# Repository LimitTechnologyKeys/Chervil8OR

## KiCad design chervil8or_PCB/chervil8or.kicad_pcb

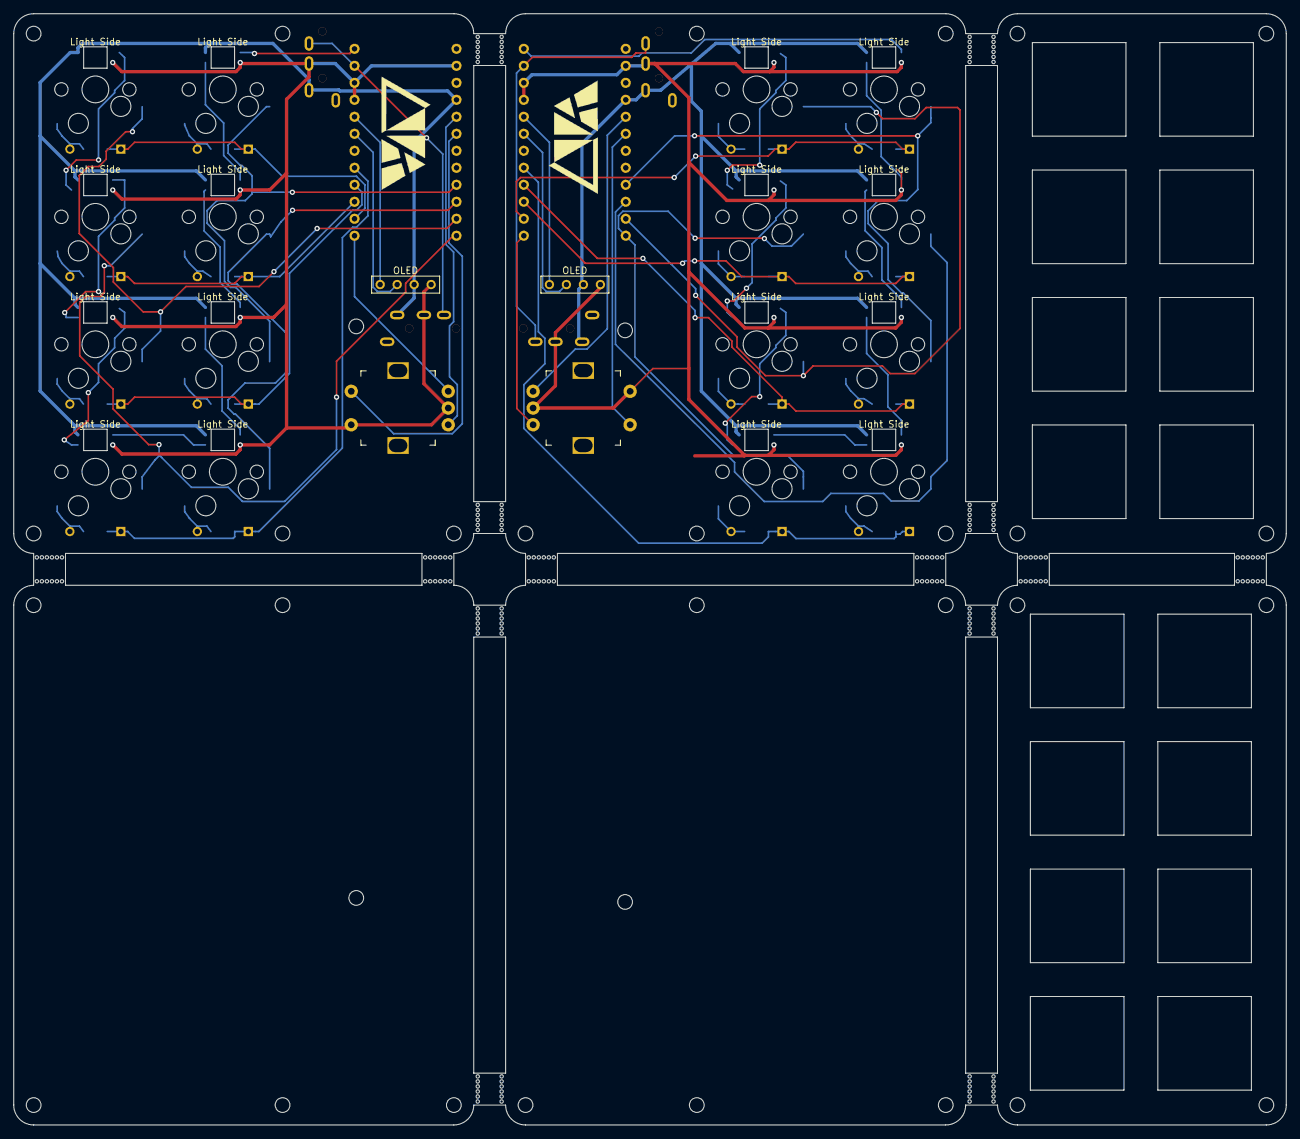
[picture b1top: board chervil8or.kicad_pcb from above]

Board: 2 copper layers, 190.2 x 166.1 mm, 118 parts (0 on the bottom side), 64 nets.

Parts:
D1, D2, D3, D4, D5, D6, D7, D8, D9, D10, D11, D12, D13, D14, D15, D16: D; Diode_TH_SMD
J1, J2, J3, J4: TRRS_MJ-4PP-9
LED1, LED2, LED3, LED4, LED5, LED6, LED7, LED8, LED9, LED10, LED11, LED12, LED13, LED14, LED15, LED16: LED_SK6812MINI-E; LED_SK6812MINI-E_BL
OL1, OL2: OLED
R16: Val16; m2_Screw_Hole
Ref1: Val1; Mouse_Bite_Hole
Ref2: Val2; Mouse_Bite_Hole
Ref3: Val3; Mouse_Bite_Hole
Ref4: Val4; Mouse_Bite_Hole
Ref5: Val5; Mouse_Bite_Hole
Ref6: Val6; Mouse_Bite_Hole
Ref7: Val7; Mouse_Bite_Hole
Ref8: Val8; Mouse_Bite_Hole
Ref9: Val9; Mouse_Bite_Hole
Ref10: Val10; Mouse_Bite_Hole
Ref11: Val11; Mouse_Bite_Hole
Ref12: Val12; Mouse_Bite_Hole
Ref13: Val13; Mouse_Bite_Hole
Ref14: Val14; Mouse_Bite_Hole
Ref15: Val15; Mouse_Bite_Hole
Ref16: Val16; Mouse_Bite_Hole
Ref17: Val17; Mouse_Bite_Hole
Ref18: Val18; Mouse_Bite_Hole
Ref19: Val19; Mouse_Bite_Hole
Ref20: Val20; Mouse_Bite_Hole
Ref21: Val21; Mouse_Bite_Hole
Ref22: Val22; Mouse_Bite_Hole
Ref23: Val23; Mouse_Bite_Hole
Ref24: Val24; Mouse_Bite_Hole
Ref26: Val26; Mouse_Bite_Hole
Ref27: Val27; Mouse_Bite_Hole
Ref28: Val28; Mouse_Bite_Hole
Ref29: Val29; Mouse_Bite_Hole
Rf1: Val1; m2_Screw_Hole
Rf2: Val2; m2_Screw_Hole
Rf3: Val3; m2_Screw_Hole
Rf4: Val4; m2_Screw_Hole
Rf5: Val5; m2_Screw_Hole
Rf6: Val6; m2_Screw_Hole
Rf7: Val7; m2_Screw_Hole
Rf8: Val8; m2_Screw_Hole
Rf9: Val9; m2_Screw_Hole
Rf10: Val10; m2_Screw_Hole
Rf11: Val11; m2_Screw_Hole
Rf12: Val12; m2_Screw_Hole
Rf13: Val13; m2_Screw_Hole
Rf14: Val14; m2_Screw_Hole
Rf15: Val15; m2_Screw_Hole
Rf17: Val17; m2_Screw_Hole
Rf18: Val18; m2_Screw_Hole
Rf19: Val19; m2_Screw_Hole
Rf20: Val20; m2_Screw_Hole
Rf21: Val21; m2_Screw_Hole
Rf22: Val22; m2_Screw_Hole
Rf23: Val23; m2_Screw_Hole
Rf24: Val24; m2_Screw_Hole
Rf25: Val25; m2_Screw_Hole
Rf26: Val26; m2_Screw_Hole
Rf27: Val27; m2_Screw_Hole
Rf28: Val28; m2_Screw_Hole
Rf29: Val29; m2_Screw_Hole
Rf30: Val30; m2_Screw_Hole
Rf31: Val31; m2_Screw_Hole
Rf32: Val32; m2_Screw_Hole
SW1, SW2, SW3, SW4, SW5, SW6, SW7, SW8, SW10, SW11, SW12, SW13, SW14, SW15, SW16, SW17: SW_PUSH; CherryMX_Hotswap_1u
SW9, SW18: Rotary_Encoder_Switch; RotaryEncoder_EC12E
U1, U2: ProMicro; Micon_ProMicro

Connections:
Col0: SW1.1, SW2.1, U1.13
Col0r: SW10.1, SW11.1, U2.13
Col1: SW3.1, SW4.1, U1.14
Col1r: SW12.1, SW13.1, U2.14
Col2: SW5.1, SW6.1, U1.15
Col2r: SW14.1, SW15.1, U2.15
Col3: SW7.1, SW8.1, U1.16
Col3r: SW16.1, SW17.1, U2.16
Col6: SW9.S1, U1.19
Col6r: SW18.S1, U2.19
Col7: SW9.A, U1.20
Col7r: SW18.A, U2.20
Col8: SW9.B, U1.12
Col8r: SW18.B, U2.12
GND: J1.C, J2.C, LED1.2, LED2.2, LED3.2, LED4.2, LED5.2, LED6.2, LED7.2, LED8.2, OL1.4, SW9.C, SW9.S2, U1.3, U1.4, U1.23
GNDr: J3.C, J4.C, LED9.2, LED10.2, LED11.2, LED12.2, LED13.2, LED14.2, LED15.2, LED16.2, OL2.4, SW18.C, SW18.S2, U2.3, U2.4, U2.23
LED: LED1.3, U1.1
LEDr: LED9.3, U2.1
unnamed: D1.2, SW1.2
unnamed: D2.2, SW2.2
unnamed: D3.2, SW3.2
unnamed: D4.2, SW4.2
unnamed: D5.2, SW5.2
unnamed: D6.2, SW6.2
unnamed: D7.2, SW7.2
unnamed: D8.2, SW8.2
unnamed: D9.2, SW10.2
unnamed: D10.2, SW11.2
unnamed: D11.2, SW12.2
unnamed: D12.2, SW13.2
unnamed: D13.2, SW14.2
unnamed: D14.2, SW15.2
unnamed: D15.2, SW16.2
unnamed: D16.2, SW17.2
unnamed: LED1.1, LED2.3
unnamed: LED2.1, LED3.3
unnamed: LED3.1, LED4.3
unnamed: LED4.1, LED5.3
unnamed: LED5.1, LED6.3
unnamed: LED6.1, LED7.3
unnamed: LED7.1, LED8.3
unnamed: LED10.1, LED11.3
unnamed: LED9.1, LED10.3
unnamed: LED11.1, LED12.3
unnamed: LED12.1, LED13.3
unnamed: LED13.1, LED14.3
unnamed: LED14.1, LED15.3
unnamed: LED15.1, LED16.3
Row0: D3.1, D7.1, U1.11
Row0r: D11.1, D15.1, U2.11
Row1: D1.1, D5.1, U1.10
Row1r: D9.1, D13.1, U2.10
Row2: D4.1, D8.1, U1.9
Row2r: D12.1, D16.1, U2.9
Row3: D2.1, D6.1, U1.8
Row3r: D10.1, D14.1, U2.8
SCL: OL1.2, U1.6
SCLr: OL2.2, U2.6
SDA: OL1.1, U1.5
SDAr: OL2.1, U2.5
VCC: J1.D, J2.D, LED1.4, LED2.4, LED3.4, LED4.4, LED5.4, LED6.4, LED7.4, LED8.4, OL1.3, U1.21
VCCr: J3.D, J4.D, LED9.4, LED10.4, LED11.4, LED12.4, LED13.4, LED14.4, LED15.4, LED16.4, OL2.3, U2.21
deta: J1.B, J2.B, U1.2
detar: J3.B, J4.B, U2.2

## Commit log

2022-04-02 Update LICENSE
2022-04-07 add LOGO
